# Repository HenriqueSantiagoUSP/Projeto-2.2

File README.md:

# Monitoramento de Idosos com ESP32

Rede de sensores para o monitoramento contínuo e não invasivo de idosos em Instituições de Longa Permanência
(ILPIs). Projeto das disciplinas Projeto Integrativo 2 e 3 da Escola Politécnica da USP.

- **Hub do quarto** (ESP32-S3):
  - presença (HC-SR501), temperatura (LM35DZ) e portas (reed switch MC-38, quantas forem necessárias);
  - roda as regras de alerta (saída noturna, banheiro, inatividade, temperatura);
  - integra o barramento CAN da sala;
  - publica tudo via MQTT.
- **Pulseira** (ESP32-S3): o dispositivo que o residente usa no pulso, com MPU-6050; detecta a queda e avisa o
  hub por ESP-NOW.

No protótipo, o hub e a pulseira são a mesma PCB com firmwares diferentes. Desde 2026-11-17 o nome é sempre
**pulseira** (antes, "vestível"); no código C, em inglês, ela é `gadget`/`wearable`.
- **Central:** Mosquitto, Grafana (estado de todos os quartos e histórico) e Telegram para o cuidador. No
  futuro, banco de dados, backend e nuvem.

```
Pulseira ──ESP-NOW──▶ Hub do quarto ──MQTT──▶ Mosquitto ─┬─▶ Telegraf ─▶ InfluxDB ─▶ Grafana
                          │                               └─▶ notificador ─▶ Telegram
                          └──CAN──▶ demais módulos da sala
```

## Estrutura

```
projeto/
├── CLAUDE.md            contexto para o Claude Code
├── docs/
│   ├── protocolo.md     contrato entre placas e central (fonte única da verdade)
│   ├── arquitetura.md   dispositivos, regras, central e estado atual
│   ├── requisitos.md    requisitos vigentes e plano de avaliação
│   ├── roadmap.md       plano de implementação em fases
│   ├── estado.md        em que etapa estamos e o que já foi verificado
│   ├── decisoes.md      histórico das decisões e o que dá para melhorar
│   └── coleta-de-dados.md  protocolo de ensaios para o futuro modelo de queda
├── firmware/
│   ├── room/            hub do quarto (ESP-IDF)
│   ├── gadget/          pulseira (ESP-IDF)
│   └── common/          componentes das duas placas: contrato, rede, MQTT, CAN, RTOS, LED
├── interface/           central em Docker Compose + simulador; legado/ = demonstração de 18/09
├── hardware/            esquemáticos, PCB e mapa de pinos
├── relatorios/          enunciados e entregas por semestre e projeto
└── aulas/               slides das aulas (molde do firmware)
```

## Início rápido

**Central sem hardware** — detalhes em [`interface/README.md`](interface/README.md):

```powershell
cd interface
copy .env.example .env                 # e troque as senhas
docker compose up -d                   # Grafana em http://localhost:3000
python simulador.py --host <IP da máquina> --senha <MQTT_HUB_PASSWORD do .env>
```

**Firmware** (ESP-IDF 6.0.1, alvo `esp32s3`) — detalhes em [`firmware/room/README.md`](firmware/room/README.md)
e [`firmware/gadget/README.md`](firmware/gadget/README.md). Para conferir uma PCB recém-soldada, o teste de
hardware [`firmware/hwtest/`](firmware/hwtest/README.md) lê todas as peças com uma gravação só:

```powershell
cd firmware\room
idf.py menuconfig                      # Wi-Fi, broker, pareamento com a pulseira
idf.py build
idf.py -p COMx flash monitor
```

Em que etapa o projeto está: [`docs/estado.md`](docs/estado.md). O que falta fazer: [`docs/pendencias.md`](docs/pendencias.md).

## Documentação

- [Arquitetura](docs/arquitetura.md)
- [Protocolo](docs/protocolo.md)
- [Requisitos](docs/requisitos.md)
- [Roadmap](docs/roadmap.md)
- [Estado atual](docs/estado.md)
- [Pendências: o que falta fazer](docs/pendencias.md)
- [Decisões e revisões](docs/decisoes.md)
- [Coleta de dados](docs/coleta-de-dados.md)
- [Relatórios e enunciados](relatorios/README.md)

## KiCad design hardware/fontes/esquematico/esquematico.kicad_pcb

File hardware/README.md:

# hardware

| Pasta | Conteúdo |
|---|---|
| `fontes/` | o que se edita: o projeto do KiCad (esquema **e layout**, em `fontes/esquematico/`), a biblioteca do projeto (`projeto.pretty`), modelos 3D e simulações (ex.: o LM358 de G = 5,5 do LM35DZ) |
| `placas/` | o que o KiCad gera para fabricar, uma pasta por versão (ex.: `placas/v1/`): Gerber, furação, PDFs do esquema e da fabricação, lista de materiais, imagens 3D e o `.zip` enviado ao fabricante |

## PCB única (primeiro projeto)

O primeiro projeto é **uma só PCB para as duas placas**: uma placa-base em que a **ESP32-S3-DevKitC-1** é
encaixada e que leva os periféricos do hub e da pulseira. Só o firmware muda: o hub usa as portas, o PIR e o
LM35; a pulseira usa o MPU-6050 e o botão; os dois usam o CAN e o LED da DevKit. Por isso nenhuma função
divide pino com outra.

Por que uma placa só: a disciplina imprime um único modelo de placa por grupo, então o hub e a pulseira tinham
de caber no mesmo projeto. Por ser um protótipo, isso não atrapalha os testes.

O mapa vale para o firmware em `firmware/common/pcb/include/pcb_pins.h`. Ele é verificado na compilação: o
build falha se dois sinais caírem no mesmo GPIO, se algum cair num pino proibido ou reservado, ou se um sinal
estiver num pino que não serve para ele (analógico fora do ADC1, por exemplo). O `board_pins.h` de cada placa
só escolhe e dá nome ao que ela usa. Se um dia as placas se separarem, o mapa de cada uma vai para o
`board_pins.h` dela.

**Situação:** proposta para o esquemático, a confirmar no layout (DRC) da PCB.

### Regras de escolha

Fontes: documentação do ESP-IDF v6.0.1 para o ESP32-S3 (GPIO, JTAG, ULP RISC-V) e a aula de PCB
(`aulas/Semestre 2/CEM_Projeto_PCB.pdf`). A regra é não usar pino que uma função do chip ligada no futuro
tomaria, mesmo que hoje não haja problema.

| Nível | GPIO | Por quê |
|---|---|---|
| nunca | 0, 3, 45, 46 | pinos de *strapping*: o nível no boot muda o modo da placa |
| nunca | 19, 20 | USB-Serial-JTAG: usá-los como GPIO desliga a USB nativa (console, gravação, depuração) |
| nunca | 43, 44 | UART0: o console e a gravação pela ponte USB da DevKit |
| nunca | 26–32, 33–37 | flash SPI e, nos módulos N8R8/N16R8, a PSRAM octal |
| nunca | 38, 48, 47 | 38 e 48: LED RGB da DevKitC-1 (v1.1 e v1.0). 47 e 48 são `SPICLK_P/N`, alimentados pelo `VDD_SPI`, que é de 1,8 V nos módulos com memória de 1,8 V |
| reserva | 15, 16 | `XTAL_32K_P/N`: um cristal de 32 kHz, para relógio preciso em *light sleep* na pulseira |
| expansão | 39–42 | `MTCK/MTDO/MTDI/MTMS`: JTAG por pinos. Hoje a depuração é pela USB; o que ficar aqui se perde se o JTAG por pinos for ligado |
| só analógico | ADC1: 1–10 | o ADC2 (11–20) não funciona com o Wi-Fi ligado. Todo analógico vai no ADC1, e os pinos do ADC1 ficam para analógico sempre que possível |
| I²C do ULP | 1 (SDA), 2 (SCL) | o I²C do coprocessador ULP RISC-V só aceita SDA em 1 ou 3 e SCL em 0 ou 2; tirando os de *strapping*, sobra 1/2. Com o I²C principal aí, o ULP poderá ler o MPU-6050 em *deep sleep* sem refazer a placa. Se as trilhas até o GY-521 se cruzarem, gire o módulo na placa em vez de trocar os pinos |
| acordar | RTC GPIO: 0–21 | o botão e o INT do MPU-6050 precisam ser RTC GPIO para acordar a pulseira de *deep sleep* (ext1) |

### Mapa

| GPIO | Função | Placa | Observação |
|---|---|---|---|
| 1 | I²C SDA (MPU-6050) | pulseira | par do ULP; ADC1_CH0 usado como digital |
| 2 | I²C SCL | pulseira | par do ULP; ADC1_CH1 |
| 4 | LM35 (saída do LM358) | hub | ADC1_CH3 |
| 5 | reservado: medição da bateria de uma pulseira própria no futuro (nesta PCB não há divisor) | — | ADC1_CH4 |
| 6, 7 | reserva analógica | — | ADC1_CH5 e CH6, para sensores futuros |
| 8 | PIR HC-SR501 | hub | ADC1_CH7, usado como digital |
| 9, 10 | portas 3 e 4 (opcionais) | hub | ADC1_CH8 e CH9: se faltar entrada analógica, essas portas cedem o lugar |
| 11, 12 | portas 1 (quarto) e 2 (banheiro) | hub | ADC2, mas digital: sem problema com o Wi-Fi |
| 13, 14 | CAN TX / RX | os dois | na pulseira, só em bancada (`GADGET_CAN`) |
| 17 | INT do MPU-6050 | pulseira | RTC GPIO |
| 18 | botão da pulseira (dois toques = "estou bem"; segurar = ajuda) | pulseira | RTC GPIO; pull-up interno e filtro de glitch |
| 21 | livre: o buzzer saiu em 2026-10-23 | — | |
| 39–42 | expansão (ex.: portas 5 a 8) | — | só enquanto o JTAG por pinos não for usado |
| 15, 16 | não ligar: cristal de 32 kHz | — | |
| 48 (v1.0) / 38 (v1.1) | LED WS2812 | os dois | é o da DevKit, não uma trilha da PCB; a versão se escolhe em `menuconfig` → PCB |

Ficam livres o 6 e o 7 (analógico), o 21, os 39–42 (expansão) e, se não forem montadas, as portas 3 e 4.

Na DevKitC-1 (headers J1 e J3), isso forma grupos, como pede a aula de PCB (analógico separado do que chaveia,
conectores numa borda). A ordem dos pinos é a do guia do usuário da ESP32-S3-DevKitC-1; confira na versão da
placa antes de desenhar a pegada:

```
J1 (de cima para baixo)                  J3 (de cima para baixo)
3V3, 3V3, RST                            GND, 43 (TX0), 44 (RX0)
4  LM35        ┐ bloco analógico         1  I²C SDA  ┐ MPU-6050
5  reservado   │ junto ao 3V3            2  I²C SCL  ┘
6  reserva     │                         42 ┐
7  reserva     ┘                         41 │ expansão
15, 16  (cristal 32 kHz: não ligar)      40 │
17 INT do MPU                            39 ┘
18 botão                                 38 (LED v1.1), 37–35 (PSRAM)
8  PIR         ┐                         0 (BOOT), 45, 48 (LED v1.0), 47
3, 46 (strapping: não ligar)│ entradas   21 livre
9  porta 3     │ do quarto,              20, 19 (USB)
10 porta 4     │ para os conectores      GND, GND
11 porta 1     │
12 porta 2     ┘
13 CAN TX      ┐ transceptor junto
14 CAN RX      ┘ à borda
5V, GND
```

Para acrescentar uma porta, basta uma linha em `BOARD_DOORS` no `board_pins.h` do hub. O firmware cria a
entrada, o tópico `porta/<id>` e o ID CAN. São **até 8 portas**, uma por nibble CAN (`0x0F3`–`0x0FA`): as 4 da
placa e as 4 da expansão. O build falha se passar disso.

O CAN da pulseira existe só para o requisito da disciplina e para os testes em bancada: a pulseira de verdade
não tem transceptor e fala com o hub por ESP-NOW.

### Condicionamento do LM35 (decidido em 2026-10-21)

O circuito validado no S1 continua: LM35DZ em 5 V e LM358 não inversor com G = 1 + 9 kΩ / 2 kΩ = 5,5. Na PCB
nova, mudam três coisas:

1. **Sem o inversor de −5 V.** O LM358 passa a ter alimentação simples: 5 V no V+ (pino 8) e GND no V−
   (pino 4). Isso está dentro do datasheet (*single supply*, 3 V a 32 V), e nessa condição:
   - a entrada aceita de 0 V até ~3,5 V; o LM35 dá no máximo 0,6 V;
   - a saída vai de ~0,02 V até ~3,5 V; o circuito usa de 0,66 V a 1,68 V entre 10 °C e 30 °C, e no máximo
     3,07 V a 57 °C.

   Com isso saem da placa:
   - a fonte de ruído chaveada no bloco analógico;
   - as peças do inversor;
   - o risco de tensão negativa no pino da ESP32.
2. **Desacoplamento:** 100 nF cerâmico (X7R) colado ao pino de alimentação do LM35 e do LM358. Os dois saem
   direto do 5 V da placa. Um ramo de 5 V separado para o analógico (ferrite ou 10 Ω, mais 10 µF) foi
   avaliado e **dispensado** (decisão de 2026-10-23):
   - o LM35 quase ignora o ruído da alimentação (regulação de linha de ~0,01 mV/V);
   - o LM358 rejeita bem o ruído lento;
   - o ruído rápido, o filtro RC abaixo corta.
3. **Filtro RC na entrada do ADC:** 10 kΩ em série da saída do LM358 (pino 1) até o GPIO 4, e 1 µF cerâmico
   (X7R, PTH) do GPIO 4 ao GND, colado no pino. Eletrolítico aqui não: a fuga dele, de µA, passando pelos
   10 kΩ, daria dezenas de mV de erro.
   - É um passa-baixa de 1ª ordem: fc = 1 / (2π · 10 kΩ · 1 µF) ≈ 16 Hz.
   - Atenua −12 dB em 60 Hz e −36 dB em 1 kHz.
   - Fica abaixo do Nyquist de 50 Hz das rajadas do firmware (16 amostras a cada 10 ms) e muito acima da banda
     do sinal (a temperatura muda em minutos). Acomoda em ~50 ms (5τ).
   - O capacitor fornece a carga do capacitor de amostragem do ADC. A documentação do ESP-IDF v6.0.1 recomenda
     um bypass de 100 nF na entrada do ADC; com 1 µF o fc desce para baixo dos 60 Hz.
   - O resistor também protege o pino: limita a corrente quando a saída sai da faixa (*back-powering* ao ligar
     a placa, LM35 com mau contato, ponta de prova no 5 V).
   - A queda nele é desprezível: só passa a fuga do pino, da ordem de nA, ou seja, menos de 1 mV.
   - Sem tensão negativa na placa, o diodo de *clamp* (BAT54S) é dispensável.

A outra metade do LM358 (pinos 5, 6 e 7) fica como seguidor em 0 V: o pino 5 no GND e o 6 ligado ao 7. Uma
entrada solta pode fazer essa metade oscilar.

| Pino do LM358 | Liga em |
|---|---|
| 8 (V+) | 5 V da placa, com 100 nF ao GND junto do pino |
| 4 (V−) | GND |
| 3 (IN+ A) | saída do LM35 |
| 2 (IN− A) | R1 = 2 kΩ ao GND e R2 = 9 kΩ ao pino 1 (9,1 kΩ na série E24: G = 5,55, compatível com o ganho medido de 5,56) |
| 1 (OUT A) | 10 kΩ até o GPIO 4; 1 µF do GPIO 4 ao GND |
| 5 / 6, 7 | GND / ligados entre si |

**Firmware e calibração:** o firmware não muda. O LM35, o ganho e os resistores são os mesmos, então a curva
`T = (V_mV − 144,739) / 51,3335` continua valendo. Na placa nova, basta conferir 3 ou 4 pontos (perto de 10,
20 e 30 °C), medindo a tensão já no GPIO 4, depois do filtro.

**Posição:** longe da DevKit e do regulador, que esquentam com o Wi-Fi, numa ponta da borda dos conectores (é a
borda que fica na abertura da caixa, onde chega o ar do quarto):
- a ponta mais longe do módulo e, se a placa ficar em pé, a de baixo, porque o ar quente sobe da ESP;
- não colado na entrada USB-C (diodo) nem no transceptor CAN.

No TO-92, os terminais de cobre são o principal caminho do calor até o chip (datasheet do LM35, montagem). Por
isso:
- recorte na placa entre o LM35 e o resto, passando só as trilhas;
- sem plano de cobre em volta dele: o GND chega por trilha (área proibida para a zona de cobre no KiCad);
- o LM35 montado alguns milímetros acima da placa, sem cortar os terminais rente.

Se ele for para um cabo, entram 1 a 2 kΩ em série na saída do LM35 (ele oscila com carga capacitiva) e
TVS/ESD no conector.

### Alimentação (decidida em 2026-10-23)

A placa tem **uma entrada só**, um módulo USB-C, e não carrega bateria:
- o **hub** é alimentado por um carregador de tomada;
- a **pulseira** (protótipo), por um **power bank** na mesma entrada.

Como só existe uma entrada, nunca há duas fontes juntas.

```
 USB-C  V ──●── +5V ──┬── C 10 µF ── GND
                      ├──▶ D1 1N5819 ──▶ pino 5V da DevKit
                      └──▶ LM35, LM358, PIR
        G ──── GND
```

| Peça | Detalhe |
|---|---|
| Módulo USB-C (V, D−, D+, G) | não tem os resistores de 5,1 kΩ no CC: **só liga com cabo USB-A → C**. D− e D+ sem conexão |
| C 10 µF eletrolítico | na saída V do módulo, junto ao conector (+ no `+5V`) |
| D1 1N5819 | do `+5V` ao pino 5V da DevKit (faixa do lado da DevKit), para não juntar duas fontes quando a USB da DevKit for ligada para gravar |

- **Fonte do hub:** carregador USB-A de 1 A ou mais, com cabo A → C.
- **Fonte da pulseira:** power bank **com saída USB-A**, ligado pelo mesmo cabo A → C. Um de 5000 mAh deve durar
  ~20–25 h com o consumo atual (estimativa).
  - Muitos power banks desligam sozinhos abaixo de ~50–100 mA. Hoje a placa puxa ~110–130 mA, mas com o *light
    sleep* o consumo cai, e aí é preciso um modelo com modo "always on" ou de baixa corrente. Alguns desses modos
    duram só ~2 h: confirmar com um teste.
- **Sem medição de bateria:** a pulseira manda a bateria como desconhecida (`0xFFFF`), e o alerta `bateria_baixa`
  não dispara. Quem mostra a carga são os LEDs do power bank.
- **Descartado nesta versão:** bateria LiPo com TP4056, boost MT3608 e troca automática por diodo. Funcionaria,
  mas toma tempo e aumenta a placa, num protótipo que já junta as duas placas numa só. Fica para a placa própria
  da pulseira: LiPo + regulador LDO de 3,3 V, mais leve e eficiente ([`docs/decisoes.md`](../docs/decisoes.md)).

### Recomendações para o esquemático e o layout

Da aula de PCB, aplicadas a este mapa:

- **Agrupar por função:** o bloco analógico fica do lado do GPIO 4 (J1 da DevKit), longe do transceptor CAN e do
  I²C. O retorno do terra analógico não divide caminho com o digital. Dentro do bloco:
  - LM35 e LM358 juntos, longe da DevKit (calor, ver a posição do LM35), com a trilha LM35 → LM358 curta: é o
    sinal pequeno (10 mV/°C), em que 1 mV de ruído já é 0,1 °C;
  - o sinal já amplificado segue até o GPIO 4, e o RC (10 kΩ + 1 µF) fica junto ao GPIO 4;
  - essa trilha não corre em paralelo ao I²C, ao CAN nem às trilhas das portas e do PIR; se precisar cruzar
    alguma, cruza a 90°, com o plano de terra inteiro embaixo.
- **Conectores numa borda só** (portas, CAN, alimentação), com o filtro de cada sinal junto ao conector:
  - nas portas, que chegam por fios longos (antenas), RC e TVS/ESD;
  - no CAN, transceptor de 3,3 V e terminação de 120 Ω quando a placa estiver numa ponta do barramento.
- **PIR (HC-SR501, encaixado na placa pelo J2):** o módulo fica deitado sobre a placa, com o domo para fora, e
  ocupa ~24 × 32 mm (o courtyard do footprint).
  - **Longe da antena da ESP**, na metade oposta da placa: o HC-SR501 tem muitos relatos de disparo falso
    perto do Wi-Fi. Com a placa em pé, isso também o tira de cima do ar quente da ESP.
  - Sem componentes embaixo dele: os dois trimpots e o jumper ficam virados para a placa. Para ajustar, tira-se
    o módulo do soquete. Trilhas por baixo podem passar.
  - O domo precisa sair por um furo na tampa da caixa: acrílico e vidro barram o infravermelho que ele vê.
  - O 100 nF da alimentação junto ao pino de 5 V do J2.
  - Opcional: um espaçador M2 de náilon do lado oposto ao soquete, se o módulo tiver os furos de fixação, para
    ele não ficar balançando só nos 3 pinos.
- **Analógico:**
  - o LM35: ver [Condicionamento do LM35](#condicionamento-do-lm35-decidido-em-2026-10-21);
- **Estado no boot:** enquanto a ESP reinicia, os pinos ficam em alta impedância.
  - Pull-up no CAN TX, para o barramento ficar recessivo.
- **Desacoplamento:** 100 nF em cada pino de alimentação dos CIs, com vias curtas ao plano de terra, e 1 a 10 µF
  na entrada de alimentação da placa.
- **Plano de terra** contínuo, com o mínimo de fendas sob as trilhas de sinal.

### Fabricação (decidida em 2026-10-23)

A placa vai para a **JLCPCB**: 2 camadas, FR-4, 1,6 mm, cobre de 1 oz, furo metalizado, HASL. Com furo
metalizado, as trilhas ficam no F.Cu e o plano de GND no B.Cu. Os limites da JLCPCB para 2 camadas são 0,127 mm
de trilha e de afastamento e via de 0,3 mm de furo por 0,5 mm de diâmetro. Os valores abaixo ficam com folga
sobre esses limites, para uma placa soldada à mão. No KiCad, ficam em *Arquivo → Configurações da placa*.

| Onde | Item | Valor |
|---|---|---|
| Regras de projeto → Restrições | afastamento mínimo / trilha mínima | 0,2 mm / 0,2 mm |
| | anel anular mínimo | 0,15 mm |
| | via: diâmetro / furo mínimos | 0,6 mm / 0,3 mm |
| | cobre até a borda / furo a furo | 0,5 mm / 0,5 mm |
| | texto da serigrafia: altura / espessura mínimas | 1,0 mm / 0,15 mm |
| Classes de rede: `Default` (sinais) | trilha / afastamento / via | 0,4 mm / 0,25 mm / 0,8 mm com furo de 0,4 mm |
| Classes de rede: `Power` (`+5V`, `+3.3V`, `GND`, `Net-(D1-K)`) | trilha / afastamento | 0,8 mm / 0,25 mm (o pico é ~0,5 A; 0,8 mm em 1 oz aguenta bem mais; em 5 V, 0,3 mm de afastamento não ganha nada e trava trilhas entre pinos) |
| Tamanhos predefinidos | trilhas / via | 0,25 (só em trecho apertado), 0,4, 0,8 e 1,0 mm / 0,8 × 0,4 mm |
| Texto e gráficos → Padrões | serigrafia: linha / texto | 0,15 mm / 1,0 × 1,0 mm, espessura 0,15 mm |
| Empilhamento | espessura / cobre | 1,6 mm / 35 µm (1 oz) |

**Pads:** os dos footprints da biblioteca servem (anel de 0,3 a 0,55 mm), com duas exceções:
- **LM35:** o `TO-92_Inline` tem anel de só 0,15 mm, difícil de soldar à mão. O `TO-92_Inline_Wide` (passo de
  2,54 mm, pad de 1,5 mm, furo de 0,8 mm) dá 0,35 mm; basta abrir um pouco os terminais.
- **DevKit:** o footprint da Espressif tem furo de 0,8 mm e pad de 1,2 × 2,0 mm. O terminal quadrado de 0,64 mm
  de uma barra de pinos tem 0,9 mm de diagonal e não entra. Usar furo de 1,0 mm com pad **oval de 1,4 × 2,2 mm**,
  estreito no sentido da fileira: o anel fica com 0,2 mm nos lados e 0,6 mm nas pontas, e sobra 1,14 mm entre
  dois pinos, onde passa uma trilha de 0,4 mm. Com pad redondo de 1,7 mm, sobrariam 0,84 mm, e nem a trilha de
  0,4 mm passaria; daria para trocar trilhas para o outro lado da DevKit só com 0,25 mm.

**Pedido:** a JLCPCB grava um número de pedido na serigrafia. Para escolher onde, pôr o texto `JLCJLCJLCJLC` no
F.Silkscreen numa área livre e marcar "Specify a location" no pedido. O preço promocional vale para placas de
até 100 × 100 mm.

## Mapas anteriores (só histórico)

Os relatórios tiveram três mapas diferentes. Nenhum serve mais:

| Função | S1 P2 (DevKit) | PCB do S1 P3 | Proposta de 2026-10-20 (antes da PCB única) |
|---|---|---|---|
| CAN TX / RX | — | 43 / 44 | 4 / 5 |
| PIR HC-SR501 | 4 | 12 | 17 |
| Portas (reed MC-38) | 5 | 48 | 18, 16 |
| LM35 (saída condicionada) | 1 (ADC1_CH0) | 18 (ADC2_CH7) | 1 |
| MPU-6050 SDA / SCL, INT | 8 / 9 | 35 / 36 | 8 / 9, INT 10 |
| Botão, buzzer (pulseira) | — | — | 11, 12 |
| Bateria | — | — | 2 |

Conflitos que a PCB do S1 tinha, todos cobertos pelas regras acima: o LM35 no ADC2 (GPIO18), o CAN no UART0
(43/44), o reed no LED da DevKit (48) e o MPU na PSRAM octal (35/36).

## Notas de componentes

- **HC-SR501:** alimentação de 5 V (pino 5V da DevKit), saída de 3,3 V compatível com o GPIO; precisa de
  ~60 s de aquecimento; modo H (*retriggerable*).
- **MC-38:** contato seco ao GND com pull-up interno, sem resistor externo; precisa de debounce. O firmware
  liga também o filtro de glitch do GPIO (pulsos de poucos ns), útil com fios longos até a porta.
- **LM35DZ:**
  - alimentado com 5 V; a Tabela 4 do relatório do S1 P3, que diz 3,3 V, está errada;
  - condicionamento: LM358 não inversor com G = 5,5 (R1 = 2 kΩ, R2 = 9 kΩ na PCB do S1), com desacoplamento
    de 100 nF;
  - até o S1, o amp-op era alimentado com ±5 V, com o −5 V vindo de um circuito inversor; na PCB nova, só
    5 V e GND, com filtro RC na saída (ver [Condicionamento do LM35](#condicionamento-do-lm35-decidido-em-2026-10-21));
  - a 12 dB, o ADC lê até ~3,1 V, o que limita a faixa útil a cerca de 57 °C.
- **MPU-6050 (GY-521):** o módulo já traz os pull-ups do I²C (para a saída do regulador dele) e um regulador de
  3,3 V; conferir no módulo usado se ele aceita o 3V3 da DevKit na entrada.
- **CAN:** transceptor de 3,3 V e terminação de 120 Ω nas pontas do barramento.
- **Pulseira:** no protótipo, power bank na entrada USB-C; bateria própria só numa placa futura da pulseira.

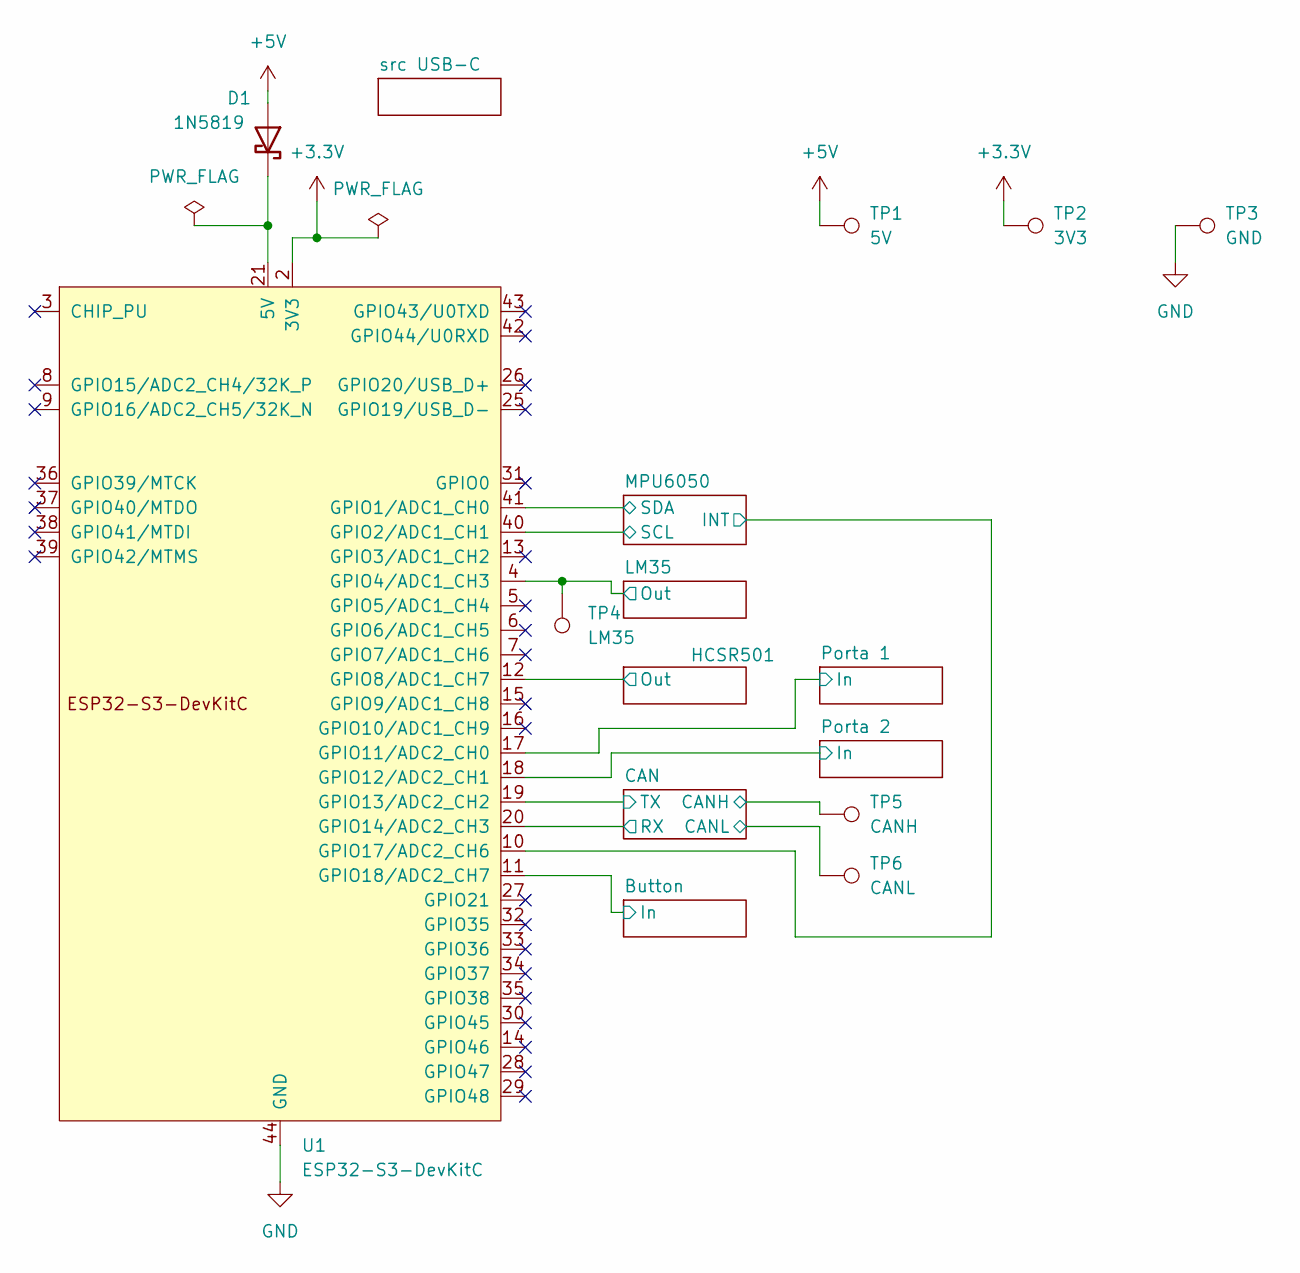
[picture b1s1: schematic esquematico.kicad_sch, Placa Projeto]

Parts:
D1: 1N5819; D_DO-41_SOD81_P10.16mm_Horizontal
TP1: 5V; TestPoint_Pad_D1.5mm
TP2: 3V3; TestPoint_Pad_D1.5mm
TP3: GND; TestPoint_Pad_D1.5mm
TP4: LM35; TestPoint_Pad_D1.5mm
TP5: CANH; TestPoint_Pad_D1.5mm
TP6: CANL; TestPoint_Pad_D1.5mm
U1: ESP32-S3-DevKitC

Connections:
+3.3V: TP2.1 (1_1), U1.1 (3V3), U1.2 (3V3); also elsewhere on the board
+5V: D1.2 (A), TP1.1 (1_1); also elsewhere on the board
/Button/In: U1.11 (GPIO18/ADC2_CH7); also elsewhere on the board
/CAN/CANH: TP5.1 (1_1); also elsewhere on the board
/CAN/CANL: TP6.1 (1_1); also elsewhere on the board
/CAN/RX: U1.20 (GPIO14/ADC2_CH3); also elsewhere on the board
/CAN/TX: U1.19 (GPIO13/ADC2_CH2); also elsewhere on the board
/HCSR501/Out: U1.12 (GPIO8/ADC1_CH7); also elsewhere on the board
/LM35/Out: TP4.1 (1_1), U1.4 (GPIO4/ADC1_CH3); also elsewhere on the board
/MPU6050/INT: U1.10 (GPIO17/ADC2_CH6); also elsewhere on the board
/MPU6050/SCL: U1.40 (GPIO2/ADC1_CH1); also elsewhere on the board
/MPU6050/SDA: U1.41 (GPIO1/ADC1_CH0); also elsewhere on the board
/Porta 1/In: U1.17 (GPIO11/ADC2_CH0); also elsewhere on the board
/Porta 2/In: U1.18 (GPIO12/ADC2_CH1); also elsewhere on the board
GND: TP3.1 (1_1), U1.22 (GND), U1.23 (GND), U1.24 (GND), U1.44 (GND); also elsewhere on the board
unnamed: D1.1 (K), U1.21 (5V)

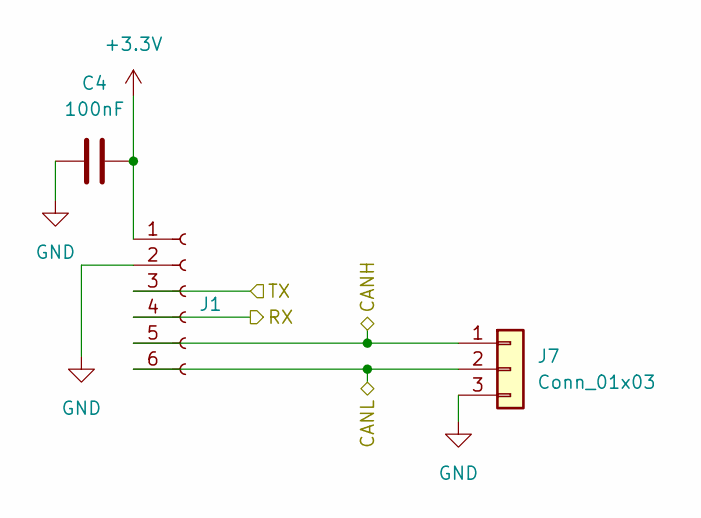
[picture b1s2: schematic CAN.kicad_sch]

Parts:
C4: 100nF; C_Disc_D3.0mm_W1.6mm_P2.50mm
J1: Conn_01x06_Socket; WCMCU-230
J7: Conn_01x03; PinHeader_1x03_P2.54mm_Vertical

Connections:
+3.3V: C4.2, J1.1; also elsewhere on the board
/CAN/CANH: J1.5, J7.1; also elsewhere on the board
/CAN/CANL: J1.6, J7.2; also elsewhere on the board
/CAN/RX: J1.4; also elsewhere on the board
/CAN/TX: J1.3; also elsewhere on the board
GND: C4.1, J1.2, J7.3; also elsewhere on the board

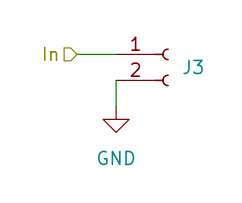
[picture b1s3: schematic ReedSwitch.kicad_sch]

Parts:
J3: Conn_01x02_Socket; PinSocket_1x02_P2.54mm_Vertical

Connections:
/Porta 1/In: J3.1; also elsewhere on the board
GND: J3.2; also elsewhere on the board

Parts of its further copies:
J4: Conn_01x02_Socket; PinSocket_1x02_P2.54mm_Vertical

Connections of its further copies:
/Porta 2/In: J4.1; also elsewhere on the board
GND: J4.2; also elsewhere on the board

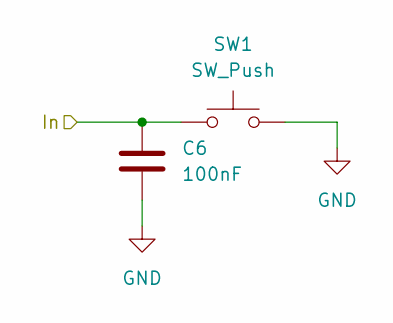
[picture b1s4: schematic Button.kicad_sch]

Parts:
C6: 100nF; C_Disc_D3.0mm_W1.6mm_P2.50mm
SW1: SW_Push; SW_PUSH-12mm

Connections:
/Button/In: C6.1, SW1.1; also elsewhere on the board
GND: C6.2, SW1.2; also elsewhere on the board

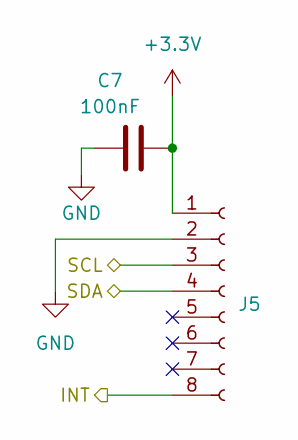
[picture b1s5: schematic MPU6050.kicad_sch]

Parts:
C7: 100nF; C_Disc_D3.0mm_W1.6mm_P2.50mm
J5: Conn_01x08_Socket; MPU6050

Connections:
+3.3V: C7.2, J5.1; also elsewhere on the board
/MPU6050/INT: J5.8; also elsewhere on the board
/MPU6050/SCL: J5.3; also elsewhere on the board
/MPU6050/SDA: J5.4; also elsewhere on the board
GND: C7.1, J5.2; also elsewhere on the board

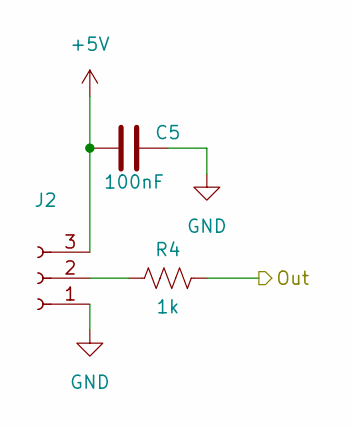
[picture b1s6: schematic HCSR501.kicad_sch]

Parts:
C5: 100nF; C_Disc_D3.0mm_W1.6mm_P2.50mm
J2: Conn_01x03_Socket; HCSR501
R4: 1k; R_Axial_DIN0207_L6.3mm_D2.5mm_P10.16mm_Horizontal

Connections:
+5V: C5.1, J2.3; also elsewhere on the board
/HCSR501/Out: R4.2; also elsewhere on the board
GND: C5.2, J2.1; also elsewhere on the board
unnamed: J2.2, R4.1

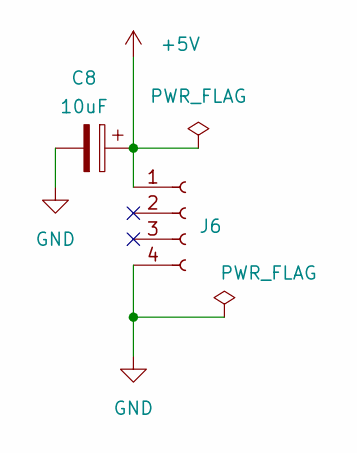
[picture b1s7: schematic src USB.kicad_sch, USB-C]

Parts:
C8: 10uF; CP_Radial_D5.0mm_P2.00mm
J6: Conn_01x04_Socket; Modulo USB-C

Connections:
+5V: C8.1, J6.1; also elsewhere on the board
GND: C8.2, J6.4; also elsewhere on the board

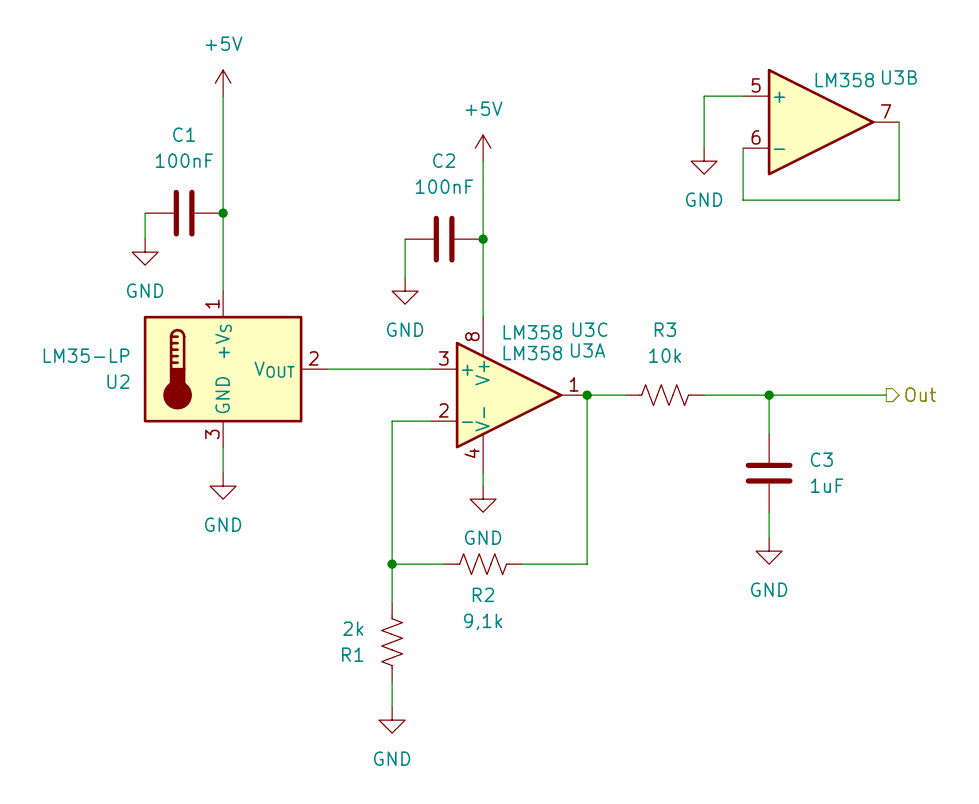
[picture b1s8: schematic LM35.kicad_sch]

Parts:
C1, C2: 100nF; C_Disc_D3.0mm_W1.6mm_P2.50mm
C3: 1uF; C_Rect_L4.0mm_W2.5mm_P2.50mm
R1: 2k; R_Axial_DIN0207_L6.3mm_D2.5mm_P10.16mm_Horizontal
R2: 9,1k; R_Axial_DIN0207_L6.3mm_D2.5mm_P10.16mm_Horizontal
R3: 10k; R_Axial_DIN0207_L6.3mm_D2.5mm_P10.16mm_Horizontal
U2: LM35-LP; TO-92_Inline_Wide
U3: LM358; DIP-8_W7.62mm_Socket_LongPads

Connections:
+5V: C1.2, C2.2, U2.1 (+V_{S}), U3.8 (V+); also elsewhere on the board
/LM35/Out: C3.1, R3.2; also elsewhere on the board
GND: C1.1, C2.1, C3.2, R1.1, U2.3 (GND), U3.4 (V-), U3.5 (+); also elsewhere on the board
unnamed: R2.2, R3.1, U3.1
unnamed: U2.2 (V_{OUT}), U3.3 (+)
unnamed: R1.2, R2.1, U3.2 (-)
unnamed: U3.6 (-), U3.7

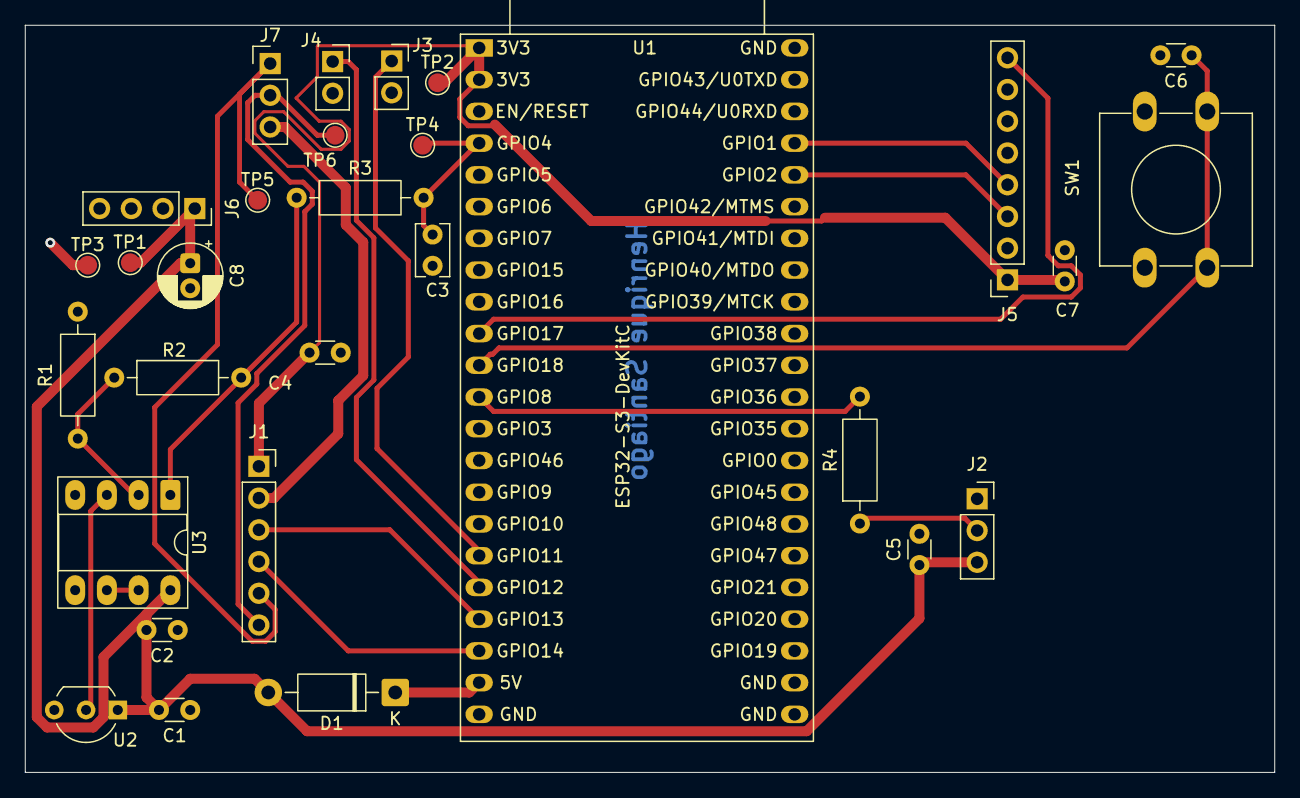
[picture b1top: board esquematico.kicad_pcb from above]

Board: 2 copper layers, 100.0 x 59.8 mm, 30 parts (0 on the bottom side), 21 nets.
